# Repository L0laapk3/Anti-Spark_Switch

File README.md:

# Anti Spark Switch
I've compacted msglazer's no-fuse design a bit. The new dimensions are 25mm x 48mm. The switch is normally open and connected to the positive input side. (Powering Vcc with the positive input side means the switch is on.) For more documentation, see msglazer's design.

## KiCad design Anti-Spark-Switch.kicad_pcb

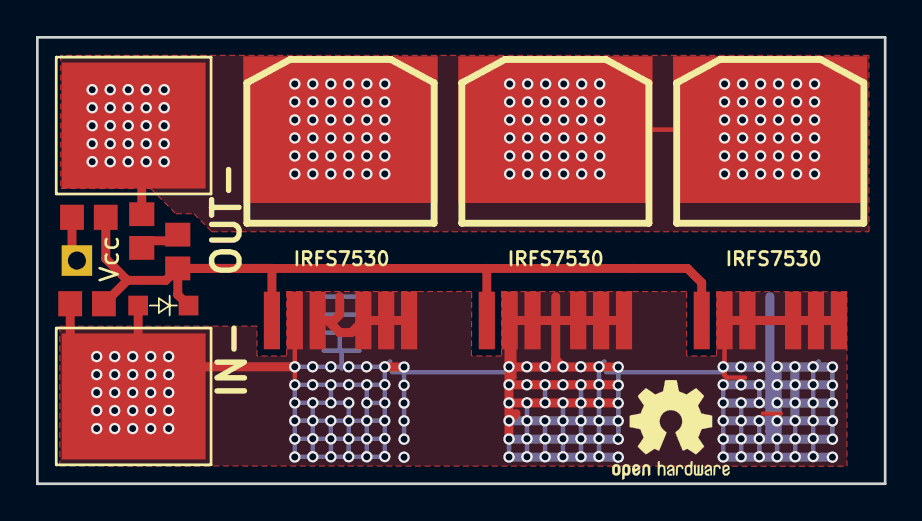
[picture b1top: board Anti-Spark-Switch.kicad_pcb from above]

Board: 2 copper layers, 47.1 x 24.8 mm, 11 parts (0 on the bottom side), 5 nets.

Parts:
1uF: 1uF; C_0805_2012Metric_Pad1.33x1.40mm_HandSolder
D1: ZENER; D_SOD-123F
IN-: Pad_Conn; 1PAD_8x7mm
OUT-: Pad_Conn; 1PAD_8x7mm
Q1, Q2, Q3: IRFS7530; D2PAK-7-GDS
R1, R2: 1M; R_0805_2012Metric_Pad1.33x1.40mm_HandSolder
R3: 1K; R_0805_2012Metric_Pad1.33x1.40mm_HandSolder
Vcc: VCC NO; PinHeader_1x01_P2.54mm_Vertical

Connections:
GND: D1.2, IN-.1, Q1.S, Q2.S, Q3.S, R2.2
unnamed: 1uF.1, R3.2
unnamed: 1uF.2, D1.1, Q1.G, Q2.G, Q3.G, R1.2, R2.1
unnamed: R1.1, Vcc.1
unnamed: OUT-.1, Q1.D, Q2.D, Q3.D, R3.1

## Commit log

2019-05-30 smaller design
2019-05-30 final changes
2019-05-30 added readme
2019-05-30 added picture
